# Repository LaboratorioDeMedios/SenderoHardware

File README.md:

Sendero Hardware
================

In this repository you will find the Eagle files to build the Bondibar LED Driver PCB and a NodeMCU V2 ESP-12E DevKit dongle PCB to ease the connection between them.

The Bondibar is a LED Strip driver using WS2801.

The Bondibar uses standard USB cables to daisychain data transmission, IRF520 high power transistors to power up up to 8 LED strips per PCB, and it can also daisychain power from one Bondibar to another. It also is capable of supplying power for the NodeMCUV2 through the USB connector.

The Bondibar was designed by Pablo Gindel (http://www.pablogindel.com) in 2013-2014 and modified for USB port power supply in 2016.

Here are some images of these components.

---------
Logo designed by flaviarampa@gmail.com & nilsonbarbara@gmail.com

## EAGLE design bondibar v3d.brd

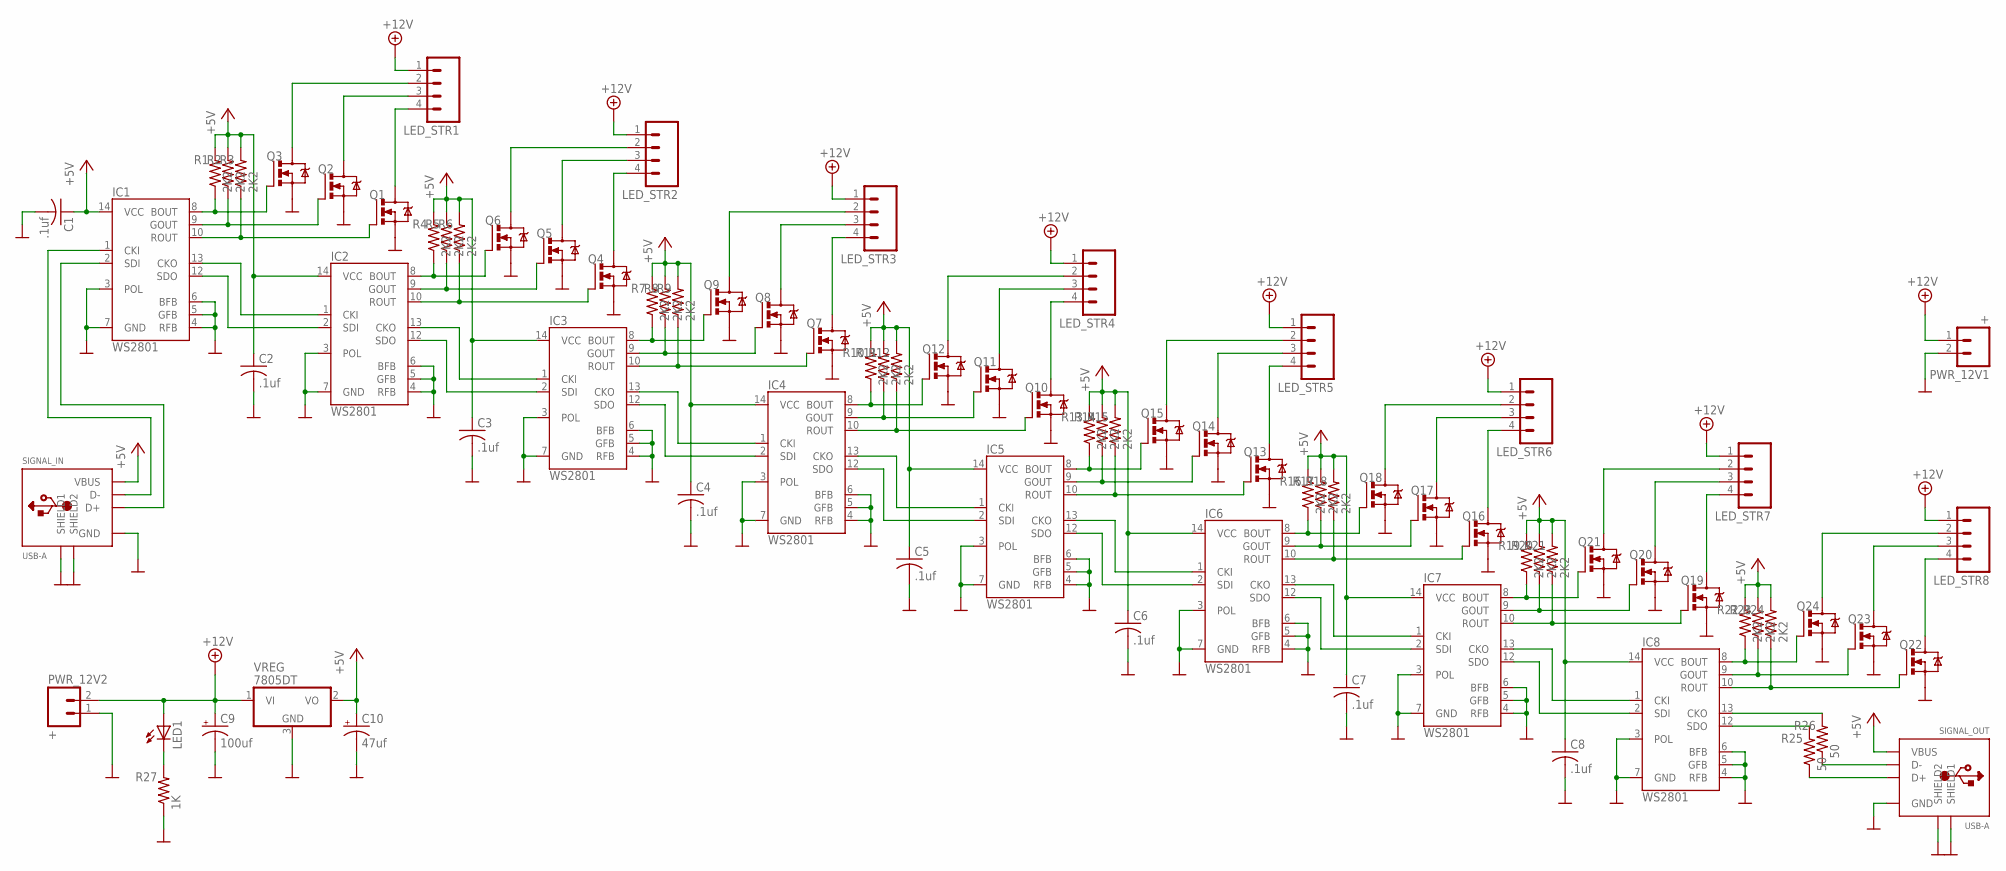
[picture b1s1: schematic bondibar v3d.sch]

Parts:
C1, C2, C3, C4, C5, C6, C7, C8: .1uf; C025-024X044
C9: 100uf; E2,5-6E
C10: 47uf; E2,5-6E
IC1, IC2, IC3, IC4, IC5, IC6, IC7, IC8: WS2801; SOP-14
LED1: LED3MM
LED_STR1, LED_STR2, LED_STR3, LED_STR4, LED_STR5, LED_STR6, LED_STR7, LED_STR8: M04PTH; 1X04
PWR_12V1, PWR_12V2: +; SCREWTERMINAL-5MM-2
Q1, Q2, Q3, Q4, Q5, Q6, Q7, Q8, Q9, Q10, Q11, Q12, Q13, Q14, Q15, Q16, Q17, Q18, Q19, Q20, Q21, Q22, Q23, Q24: IRF520; TO220BV
R1, R2, R3, R4, R5, R6, R7, R8, R9, R10, R11, R12, R13, R14, R15, R16, R17, R18, R19, R20, R21, R22, R23, R24: 2K2; 0204V
R25, R26: 50; 0204V
R27: 1K; 0204V
SIGNAL_IN: USB-A; USB_HOST-PTH
SIGNAL_OUT: USB-A; USB_HOST-PTH
VREG: 7805DT; TO252

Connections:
+5V: C1.1, C2.1, C3.1, C4.1, C5.1, C6.1, C7.1, C8.1, C10.+, IC1.14 (VCC), IC2.14 (VCC), IC3.14 (VCC), IC4.14 (VCC), IC5.14 (VCC), IC6.14 (VCC), IC7.14 (VCC), IC8.14 (VCC), R1.2, R2.2, R3.2, R4.2, R5.2, R6.2, R7.2, R8.2, R9.2, R10.2, R11.2, R12.2, R13.2, R14.2, R15.2, R16.2, R17.2, R18.2, R19.2, R20.2, R21.2, R22.2, R23.2, R24.2, SIGNAL_IN.VBUS, SIGNAL_OUT.VBUS, VREG.2 (VO)
+12V: C9.+, LED1.A, LED_STR1.1, LED_STR2.1, LED_STR3.1, LED_STR4.1, LED_STR5.1, LED_STR6.1, LED_STR7.1, LED_STR8.1, PWR_12V1.1, PWR_12V2.2, VREG.1 (VI)
DATA_IN: IC1.1 (CKI), SIGNAL_IN.D-
GND: C1.2, C2.2, C3.2, C4.2, C5.2, C6.2, C7.2, C8.2, C9.-, C10.-, IC1.3 (POL), IC1.4 (RFB), IC1.5 (GFB), IC1.6 (BFB), IC1.7 (GND), IC2.3 (POL), IC2.4 (RFB), IC2.5 (GFB), IC2.6 (BFB), IC2.7 (GND), IC3.3 (POL), IC3.4 (RFB), IC3.5 (GFB), IC3.6 (BFB), IC3.7 (GND), IC4.3 (POL), IC4.4 (RFB), IC4.5 (GFB), IC4.6 (BFB), IC4.7 (GND), IC5.3 (POL), IC5.4 (RFB), IC5.5 (GFB), IC5.6 (BFB), IC5.7 (GND), IC6.3 (POL), IC6.4 (RFB), IC6.5 (GFB), IC6.6 (BFB), IC6.7 (GND), IC7.3 (POL), IC7.4 (RFB), IC7.5 (GFB), IC7.6 (BFB), IC7.7 (GND), IC8.3 (POL), IC8.4 (RFB), IC8.5 (GFB), IC8.6 (BFB), IC8.7 (GND), PWR_12V1.2, PWR_12V2.1, Q1.S, Q2.S, Q3.S, Q4.S, Q5.S, Q6.S, Q7.S, Q8.S, Q9.S, Q10.S, Q11.S, Q12.S, Q13.S, Q14.S, Q15.S, Q16.S, Q17.S, Q18.S, Q19.S, Q20.S, Q21.S, Q22.S, Q23.S, Q24.S, R27.1, SIGNAL_IN.GND, SIGNAL_IN.S1 (SHIELD1), SIGNAL_IN.S2 (SHIELD2), SIGNAL_OUT.GND, SIGNAL_OUT.S1 (SHIELD1), SIGNAL_OUT.S2 (SHIELD2), VREG.3 (GND)
unnamed: IC1.8 (BOUT), Q3.G, R1.1
unnamed: IC1.9 (GOUT), Q2.G, R2.1
unnamed: IC1.10 (ROUT), Q1.G, R3.1
unnamed: IC2.8 (BOUT), Q6.G, R4.1
unnamed: IC2.12 (SDO), IC3.2 (SDI)
unnamed: IC2.9 (GOUT), Q5.G, R5.1
unnamed: IC2.10 (ROUT), Q4.G, R6.1
unnamed: IC1.12 (SDO), IC2.2 (SDI)
unnamed: IC2.13 (CKO), IC3.1 (CKI)
unnamed: IC1.13 (CKO), IC2.1 (CKI)
unnamed: IC3.12 (SDO), IC4.2 (SDI)
unnamed: IC3.13 (CKO), IC4.1 (CKI)
unnamed: IC4.13 (CKO), IC5.1 (CKI)
unnamed: IC3.8 (BOUT), Q9.G, R7.1
unnamed: IC3.9 (GOUT), Q8.G, R8.1
unnamed: IC3.10 (ROUT), Q7.G, R9.1
unnamed: IC4.12 (SDO), IC5.2 (SDI)
unnamed: IC5.12 (SDO), IC6.2 (SDI)
unnamed: IC5.13 (CKO), IC6.1 (CKI)
unnamed: IC6.12 (SDO), IC7.2 (SDI)
unnamed: IC6.13 (CKO), IC7.1 (CKI)
unnamed: IC7.12 (SDO), IC8.2 (SDI)
unnamed: IC4.8 (BOUT), Q12.G, R10.1
unnamed: IC4.9 (GOUT), Q11.G, R11.1
unnamed: IC4.10 (ROUT), Q10.G, R12.1
unnamed: IC7.13 (CKO), IC8.1 (CKI)
unnamed: LED_STR1.4, Q1.D
unnamed: LED_STR1.3, Q2.D
unnamed: LED_STR1.2, Q3.D
unnamed: LED_STR4.3, Q11.D
unnamed: LED_STR4.4, Q10.D
unnamed: LED_STR2.4, Q4.D
unnamed: LED_STR2.3, Q5.D
unnamed: LED_STR2.2, Q6.D
unnamed: IC5.8 (BOUT), Q15.G, R13.1
unnamed: IC5.9 (GOUT), Q14.G, R14.1
unnamed: IC5.10 (ROUT), Q13.G, R15.1
unnamed: LED_STR3.2, Q9.D
unnamed: LED_STR3.3, Q8.D
unnamed: LED_STR3.4, Q7.D
unnamed: LED_STR4.2, Q12.D
unnamed: LED_STR5.2, Q15.D
unnamed: LED_STR5.3, Q14.D
unnamed: IC6.8 (BOUT), Q18.G, R16.1
unnamed: IC6.9 (GOUT), Q17.G, R17.1
unnamed: IC6.10 (ROUT), Q16.G, R18.1
unnamed: LED_STR5.4, Q13.D
unnamed: LED_STR6.2, Q18.D
unnamed: LED_STR6.3, Q17.D
unnamed: LED_STR6.4, Q16.D
unnamed: LED_STR7.2, Q21.D
unnamed: LED_STR7.3, Q20.D
unnamed: LED_STR7.4, Q19.D
unnamed: LED_STR8.2, Q24.D
unnamed: LED_STR8.3, Q23.D
unnamed: IC7.8 (BOUT), Q21.G, R19.1
unnamed: IC7.9 (GOUT), Q20.G, R20.1
unnamed: IC7.10 (ROUT), Q19.G, R21.1
unnamed: LED_STR8.4, Q22.D
unnamed: R26.1, SIGNAL_OUT.D-
unnamed: IC1.2 (SDI), SIGNAL_IN.D+
unnamed: IC8.12 (SDO), R25.2
unnamed: R25.1, SIGNAL_OUT.D+
unnamed: IC8.13 (CKO), R26.2
unnamed: IC8.8 (BOUT), Q24.G, R22.1
unnamed: IC8.9 (GOUT), Q23.G, R23.1
unnamed: IC8.10 (ROUT), Q22.G, R24.1
unnamed: LED1.K (C), R27.2

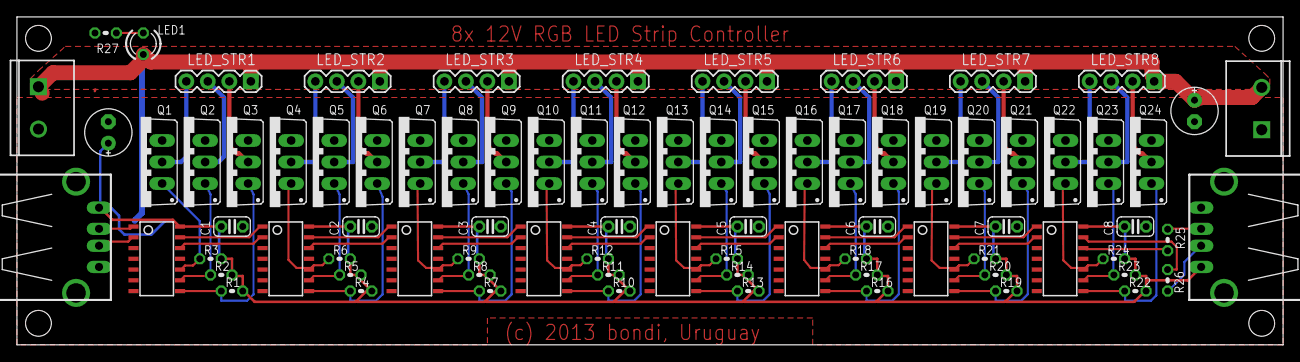
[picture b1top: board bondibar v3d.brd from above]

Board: 2 copper layers, 149.5 x 38.7 mm, 87 parts (1 on the bottom side), 72 nets.

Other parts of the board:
U$56, U$57, U$58, U$59: STAND-OFF-TIGHT

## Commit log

2016-07-10 Initial commit.

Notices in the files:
bondibar v3d.brd:
(c) 2013 bondi, Uruguay
parts and their libraries:
SparkFun-DigitalIC: Licensing: CC v3.0 Share-Alike You are welcome to use this library for commercial purposes.
